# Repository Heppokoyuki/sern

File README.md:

# SERN PROJECT REPOSITORY

## Overview
This repository is made for Hack U National Institute of Technology, Tokyo College 2018 by Team SERN 2018.

## Description
The source code in this repository has any functions for TubeBox. TubeBox is conpact and simple vacuum tube amplifier. We created client application that works on Android and browser, server application that works on Raspbian on Raspberry Pi 3, and the DAC circuit that converts I2S to analog signal. 

## Team Member
[@heppoko_yuki](https://twitter.com/heppoko_yuki)
[@car4ryu](https://twitter.com/car4ryu)
[@shibh308](https://twitter.com/shibh308)

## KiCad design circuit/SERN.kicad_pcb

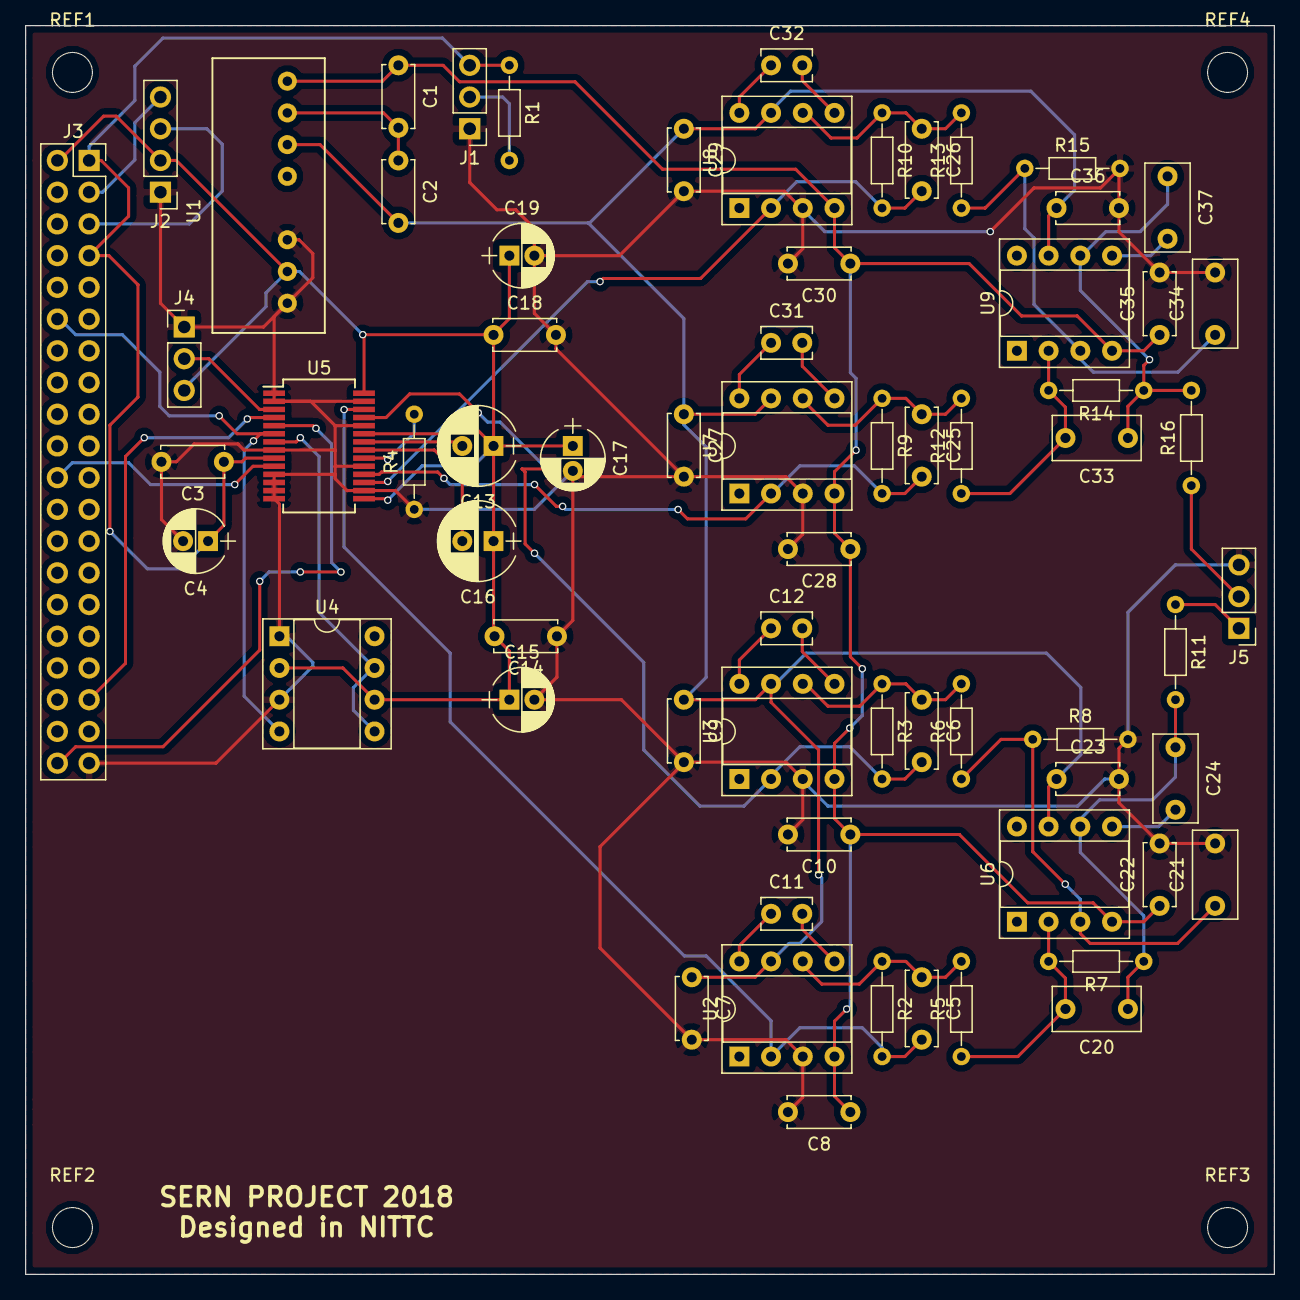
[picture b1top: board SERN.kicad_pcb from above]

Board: 2 copper layers, 100.0 x 100.0 mm, 71 parts (0 on the bottom side), 44 nets.

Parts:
C1, C2, C3, C7, C8, C9, C10, C14, C18, C22, C23, C27, C28, C29, C30, C35, C36: 0.1uF; C_Disc_D5.0mm_W2.5mm_P5.00mm
C4, C15, C17, C19: 10uF; CP_Radial_D5.0mm_P2.00mm
C5, C6, C25, C26: 2200pF; C_Disc_D6.0mm_W2.5mm_P5.00mm
C11, C12, C31, C32: 22pF; C_Rect_L4.0mm_W2.5mm_P2.50mm
C13, C16: 47uF; CP_Radial_D6.3mm_P2.50mm
C20, C21, C33, C34: 2700pF; C_Rect_L7.0mm_W3.5mm_P5.00mm
C24, C37: 33pF; C_Rect_L7.0mm_W3.5mm_P5.00mm
J1, J4, J5: Conn_01x03; Pin_Header_Straight_1x03_Pitch2.54mm
J2: Conn_01x04; Pin_Header_Straight_1x04_Pitch2.54mm
J3: RaspberryPi3; Socket_Strip_Straight_2x20_Pitch2.54mm
R1: 4.7k; R_Axial_DIN0204_L3.6mm_D1.6mm_P7.62mm_Horizontal
R2, R3, R9, R10: 750; R_Axial_DIN0204_L3.6mm_D1.6mm_P7.62mm_Horizontal
R4: 10k; R_Axial_DIN0204_L3.6mm_D1.6mm_P7.62mm_Horizontal
R5, R6, R12, R13: 560; R_Axial_DIN0204_L3.6mm_D1.6mm_P7.62mm_Horizontal
R7, R8, R14, R15: 270; R_Axial_DIN0204_L3.6mm_D1.6mm_P7.62mm_Horizontal
R11, R16: 100; R_Axial_DIN0204_L3.6mm_D1.6mm_P7.62mm_Horizontal
REF1, REF2, REF3, REF4: MountingHole_3.2mm_M3
U1: MCW03
U2, U3, U7, U8: NE5534; DIP-8_W7.62mm_Socket
U4: ICS570; DIP-8_W7.62mm_Socket
U5: pcm1794; SSOP-28_5.3x10.2mm_Pitch0.65mm
U6, U9: LT1028; DIP-8_W7.62mm_Socket

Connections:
+3V3: C3.1, C4.1, J1.3, J3.1, J3.7, R1.1, U5.9
+5V: C13.1, C14.2, C15.1, C16.1, C17.1, C18.1, C19.1, J2.2, J3.2, J4.3, U1.2, U4.2, U4.6, U5.15, U5.23, U5.28
GNDD: C3.2, C4.2, C7.2, C8.2, C9.2, C10.2, C14.1, C15.2, C17.2, C18.2, C19.2, C21.2, C22.2, C23.2, C27.2, C28.2, C29.2, C30.2, C34.2, C35.2, C36.2, J1.1, J2.1, J3.39, J4.1, J5.3, R4.1, R8.2, R15.2, U1.1, U1.3, U2.3, U3.3, U4.1, U4.3, U5.1, U5.2, U5.8, U5.11, U5.12, U5.13, U5.14, U5.16, U5.19, U5.24, U5.27, U7.3, U8.3
L+: C6.2, R3.2, U3.2, U5.25
L-: C5.2, R2.2, U2.2, U5.26
Lin: J5.1, R11.1
unnamed: C1.2, C2.1, U1.7
unnamed: C5.1, R2.1, R5.2, U2.6
unnamed: C6.1, R3.1, R6.2, U3.6
unnamed: C11.1, U2.8
unnamed: C11.2, U2.5
unnamed: C12.1, U3.8
unnamed: C12.2, U3.5
unnamed: C13.2, U5.22
unnamed: C16.2, U5.21
unnamed: C20.1, C24.1, R7.1, R11.2, U6.6
unnamed: C20.2, R5.1, R7.2, U6.2
unnamed: C21.1, R6.1, R8.1, U6.3
unnamed: C24.2, U6.5
unnamed: C25.1, R9.1, R12.2, U7.6
unnamed: C26.1, R10.1, R13.2, U8.6
unnamed: C31.1, U7.8
unnamed: C31.2, U7.5
unnamed: C32.1, U8.8
unnamed: C32.2, U8.5
unnamed: C33.1, C37.1, R14.1, R16.2, U9.6
unnamed: C33.2, R12.1, R14.2, U9.2
unnamed: C34.1, R13.1, R15.1, U9.3
unnamed: C37.2, U9.5
unnamed: J1.2, R1.2
unnamed: J2.3, J3.5
unnamed: J2.4, J3.3
unnamed: J3.12, U4.4, U5.6
unnamed: J3.22, U5.10
unnamed: J3.35, U5.4
unnamed: J3.40, U5.5
unnamed: J4.2, U5.3
unnamed: R4.2, U5.20
unnamed: U4.5, U4.7, U5.7
R+: C26.2, R10.2, U5.17, U8.2
R-: C25.2, R9.2, U5.18, U7.2
Rin: J5.2, R16.1
VCC: C2.2, C7.1, C9.1, C23.1, C27.1, C29.1, C36.1, U1.6, U2.7, U3.7, U6.7, U7.7, U8.7, U9.7
VEE: C1.1, C8.1, C10.1, C22.1, C28.1, C30.1, C35.1, U1.8, U2.4, U3.4, U6.4, U7.4, U8.4, U9.4

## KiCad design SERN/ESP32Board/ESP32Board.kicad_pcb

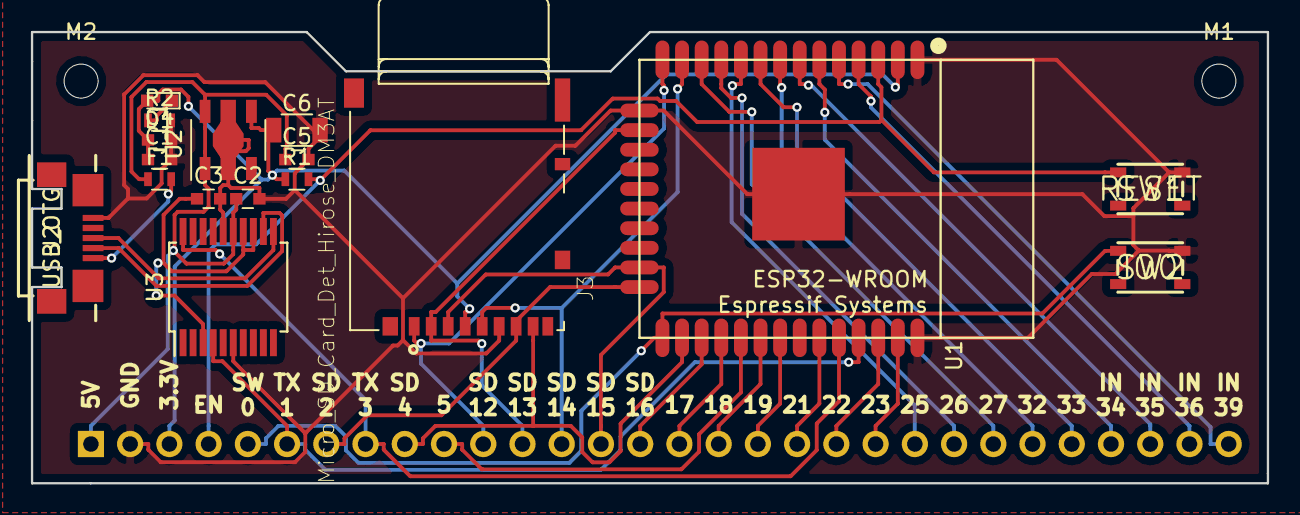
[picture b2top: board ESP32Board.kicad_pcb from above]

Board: 2 copper layers, 80.0 x 29.2 mm, 20 parts (1 on the bottom side), 35 nets.

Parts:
C1, C2, C3, C4, C5: 0.1uF; C_0603
C6: 47uF; C_1206
D1: Power; LED_0603
F1: Polyfuse_Small; R_0603
J1: Conn_01x30; Pin_Header_Straight_1x30_Pitch2.54mm
J2: USB_OTG; USB-micro-B_Hirose
J3: Micro_SD_Card_Det_Hirose_DM3AT; HRS_DM3AT-SF-PEJM5
M1, M2: MountingHole_2.2mm_M2
R1: 10k; R_0603
R2: 1k; R_0603
SW1: RESET; SKRPACE010
SW2: IO0; SKRPACE010
U1: ESP32-WROOM
U2: NJM2884; SOT-89-5_Housing
U3: FT231XS; SSOP-20_5.3x7.2mm_Pitch0.65mm

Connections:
+3V3: C1.1, C4.1, C6.1, D1.2, J1.3, J3.4, R1.1, U1.2, U2.4
+5V: C2.1, C5.1, F1.1, J1.1, U2.1, U2.5, U3.15
ENABLE: J1.4, R1.2, SW1.1, U1.3
GND: C1.2, C2.2, C3.2, C4.2, C5.2, C6.2, J1.2, J2.5, J3.6, R2.2, SW1.2, SW2.2, U1.1, U1.15, U1.38, U1.39, U2.2, U3.6, U3.16
IO0: J1.5, SW2.1, U1.25
unnamed: C3.1, U3.3, U3.13, U3.14
unnamed: D1.1, R2.1
unnamed: F1.2, J2.1
unnamed: J1.10, U1.29
unnamed: J1.16, U1.28
unnamed: J1.17, U1.30
unnamed: J1.18, U1.31
unnamed: J1.19, U1.33
unnamed: J1.20, U1.36
unnamed: J1.21, U1.37
unnamed: J1.22, U1.10
unnamed: J1.23, U1.11
unnamed: J1.24, U1.12
unnamed: J1.25, U1.8
unnamed: J1.26, U1.9
unnamed: J1.27, U1.6
unnamed: J1.28, U1.7
unnamed: J1.29, U1.4
unnamed: J1.30, U1.5
RXD: J1.8, U1.34, U3.20
SD_CLK: J1.13, J3.5, U1.13
SD_CMD: J1.14, J3.3, U1.23
SD_DETECT: J1.15, U1.27
SD_SD0: J1.7, J3.7, U1.24
SD_SD1: J1.9, J3.8, U1.26
SD_SD2: J1.11, J3.1, U1.14
SD_SD3: J1.12, J3.2, U1.16
TXD: J1.6, U1.35, U3.4
USB_D+: J2.3, U3.11
USB_D-: J2.2, U3.12

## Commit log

2017-11-05 ふぁーすとこみっと
2017-11-10 [add]add udp
2017-12-06 [remove]esp32関連のクソなのをremove
2017-12-06 [update]今更ディレクトリ作ってブランチ切ってgpmapiでログインできるようにしたよ
2017-12-06 [add] Initial commit
2017-12-06 [clean]ファイル名気持ち悪い
2017-12-06 [clean]いらないファイルを削除
2017-12-06 inital commit
2017-12-06 slack通知テスト
2017-12-17 [add]circuit
2017-12-17 [clean]
2017-12-17 [add]指定したMessageを送れるように仕様変更 !!サーバーを用いてのテストはまだ行えていない!!
2017-12-21 [update]i2s周りの信号線ひいた、あとはアナログ部分
2017-12-22 [add]アナログ信号周り
2017-12-23 [update]できた
2017-12-29 [fix]わかりにくい関数名の変更
2018-01-09 [add]BLEのInitializeコードまで追加、ボタン一つで音量の大小ができるようWebSocket側も機能を実装
2018-01-24 [completed]DAC基板できたけどLibraryの依存解決できてないのであとでやる（やるとは言ってない）
2018-01-24 [add]製造データできた
2018-01-24 [rename]
2018-01-24 [add]発注用データ
2018-02-04 [update]
2018-02-09 [add]Ping通してスキャンするやつ実装、まだUIは未完成なので実際には機能しない その他音量変更指示を送信するときのエラーを解消 BLE関連のファイルを抹消、あんなものはなかった
2018-02-22 [add]Bluetoothデバイスの検索機能を実装、コメントアウトで文字列送信まで書いてあるが未テスト
2018-02-23 [add]BluetoothDevice検索後、検索対象が見つかった場合に接続するシステムを実装、ただし未テスト、また不要なクラスを削除
2018-02-28 [fix]Bluetooth諦めた、疲れた
2018-02-28 [fix]アプリとマージできるようにアドレスや音量調整用の文字列を修正
2018-03-03 [add]about
2018-03-03 [delete]うんち
2018-03-06 [add] webApp
2018-03-06 [update]WebSocketを有効に
2018-03-06 [update].gitignore
2018-03-06 [new]README
2018-03-06 [fix]miss
2018-03-07 fix my stupid commit
2018-03-07 [add]UDPによる自動接続および改良したUIを実装(不安定)
2018-03-08 [last commit]
2018-03-08 [update]last ja naijajn
2018-03-08 [update]ip address changed
2018-03-08 [fix]Fixed some typos, and make the sentences a bit cleaner.Tiring.
2018-03-08 [fix]UI調整その1
2018-03-08 [fix]アルゴリズム少々修正
2018-03-08 [fix]接続失敗時の動作を改善、UI改良
